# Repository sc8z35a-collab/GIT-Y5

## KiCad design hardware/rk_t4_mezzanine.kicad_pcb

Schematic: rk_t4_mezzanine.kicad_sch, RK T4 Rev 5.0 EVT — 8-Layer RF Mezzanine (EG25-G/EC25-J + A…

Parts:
C701, C702, C705, C706: GRM0335C1H101JA01D; 0201
C753, C754, C1332, C1338, C1339, C1340, C1343, C1345, C1346, C1348, C1351, C1352, C1355, C1357, C1358, C1360, C1361, C1363, C1366, C1367, C1370, C1372, C1373, C1375, C1376, C1378, C1381, C1382, C1385, C1387, C1388, C1391: GRM033R61A104KE15D; 0201
C1322, C1328, C1331, C1333, C1334, C1335, C1336, C1337: GRM033R60J105MEA2D; 0201
C1323, C1324, C1329, C1330: GRM0335C1H120JA01D; 0201
C1325, C1326: GRM155R61A475MEAA; 0402
C1327: GRM155R61A106ME44D; 0402
C1341, C1342: GRM033R60J225ME15D; 0201
C1344, C1349, C1354, C1359, C1364, C1369, C1374, C1379, C1384: GRM155R60J226ME11D; 0402
C1347, C1350, C1353, C1356, C1362, C1365, C1368, C1371, C1377, C1380, C1383, C1386: GRM022R60J103ME15; 01005
FB1011, FB1012: BLM03AG121SN1D; 0201
J701, J702, J705, J706, J707: 20449-001E; MHF4-RECEPT
J708A, J708B: 2329497-2; TE-2329497-2
J901A, J901B: DF40C-40DP-0.4V(51); DF40C-40DP
L701, L702: DFE201610E-0R56M=P2; IND_1608
L711, L712: DFE201610E-2R2M=P2; IND_1608
L1001, L1002: LQG15HS47NJ02D; 0201
Q701, Q702: BSS138; SOT-23__2.9x2.4mm_
R133: RC0201FR-0710KL; 0201
R1007, R1008: RC0201FR-07100KL; 0201
R1009, R1010: RC0201FR-071KL; 0201
R1011, R1012: RC0201FR-07470RL; 0201
RT701: NCP03XH103F05RL; 0201
TP701, TP702: TP_0.8MM_ENIG; TP_0.8MM
U701: EG25-G; LGA-144__29.0x32.0mm_
U707: AP6275P; LGA-50__15.0x13.0mm_
U708: MIA-M10Q-00B; LGA-54__4.5x4.5mm_
U710: PN7160A1HN; HVQFN-40__6.0x6.0mm_
U715: IQS7222A001QNR; QFN-20__3.0x3.0mm_
U716: STSAFE-A110; UFDFPN8__2.0x3.0mm_
Y701: NX2016SA-27.12M; SMD-2016
Y702: NX2016SA-37.4M; SMD-2016

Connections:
BT_HOST_WAKE: J901B.31, U707.50 (BT_HOST_WAKE)
BT_REG_ON: J901B.29, U707.38 (BT_REG_ON)
BT_UART_CTS_N: J901B.36, U707.42 (BT_UART_RTS_N)
BT_UART_RTS_N: J901B.35, U707.43 (BT_UART_CTS_N)
BT_UART_RX: J901B.34, U707.40 (BT_UART_TXD)
BT_UART_TX: J901B.33, U707.41 (BT_UART_RXD)
BT_WAKE: J901B.30, U707.49 (BT_WAKE)
CLK_32K_RTC: J901B.32, U707.31 (LPO_IN)
EG_PWRKEY_N: Q701.3 (D), U701.21 (PWRKEY)
EG_RESET_N: Q702.3 (D), U701.20 (RESET_N)
EG_VDD_EXT_1V8: C1322.1, U701.7 (VDD_EXT)
ESE_RST_N: J901A.40, U716.8 (RESET)
GND: C1322.2, C1323.2, C1324.2, C1325.2, C1326.2, C1327.2, C1328.2, C1329.2, C1330.2, C1331.2, C1332.2, C1333.2, C1334.2, C1335.2, C1336.2, C1337.2, C1338.2, C1339.2, C1340.2, C1341.2, C1342.2, C1343.2, C1344.2, C1345.2, C1346.2, C1347.2, C1348.2, C1349.2, C1350.2, C1351.2, C1352.2, C1353.2, C1354.2, C1355.2, C1356.2, C1357.2, C1358.2, C1359.2, C1360.2, C1361.2, C1362.2, C1363.2, C1364.2, C1365.2, C1366.2, C1367.2, C1368.2, C1369.2, C1370.2, C1371.2, C1372.2, C1373.2, C1374.2, C1375.2, C1376.2, C1377.2, C1378.2, C1379.2, C1380.2, C1381.2, C1382.2, C1383.2, C1384.2, C1385.2, C1386.2, C1387.2, C1388.2, C1391.2, J701.2 (GND_1), J701.3 (GND_2), J702.2 (GND_1), J702.3 (GND_2), J705.2 (GND_1), J705.3 (GND_2), J706.2 (GND_1), J706.3 (GND_2), J707.2 (GND_1), J707.3 (GND_2), J901A.7, J901A.8, J901A.10, J901A.12, J901A.19, J901A.20, J901A.30, J901A.34, J901B.11, J901B.12, J901B.14, J901B.16, J901B.18, J901B.20, J901B.22, J901B.24, Q701.2 (S), Q702.2 (S), R1007.2, R1008.2, RT701.2, U701.8 (GND), U701.9 (GND), U701.10 (USIM_GND), U701.19 (GND), U701.22 (GND), U701.36 (GND), U701.46 (GND), U701.48 (GND), U701.50 (GND), U701.51 (GND), U701.52 (GND), U701.53 (GND), U701.54 (GND), U701.56 (GND), U701.72 (GND), U701.85 (GND), U701.86 (GND), U701.87 (GND), U701.88 (GND), U701.89 (GND), U701.90 (GND), U701.91 (GND), U701.92 (GND), U701.93 (GND), U701.94 (GND), U701.95 (GND), U701.96 (GND), U701.97 (GND), U701.98 (GND), U701.99 (GND), U701.100 (GND), U701.101 (GND), U701.102 (GND), U701.103 (GND), U701.104 (GND), U701.105 (GND), U701.106 (GND), U701.107 (GND), U701.108 (GND), U701.109 (GND), U701.110 (GND), U701.111 (GND), U701.112 (GND), U707.1 (GND), U707.3 (GND), U707.4 (GND), U707.5 (GND), U707.6 (GND), U707.7 (GND), U707.8 (GND), U707.10 (GND), U707.11 (GND), U707.23 (GND), U707.27 (GND), U707.30 (GND), U707.32 (GND), U707.39 (GND), U708.A1 (GND), U708.A2 (GND), U708.A3 (GND), U708.A5 (RTC_O), U708.A8 (GND), U708.A9 (GND), U708.B2 (GND), U708.B8 (GND), U708.C3 (GND), U708.C9 (GND), U708.E3 (GND), U708.E4 (GND), U708.E9 (GND), U708.F1 (GND), U708.F3 (GND), U708.F4 (GND), U708.F9 (GND_0R), U708.G3 (GND), U708.G4 (GND), U708.G5 (GND), U708.G6 (GND), U708.G7 (GND_0R), U708.H8 (GND), U708.J6 (VIO_SEL), U708.J8 (GND), U708.J9 (GND), U710.1 (I2C_ADR0), U710.3 (I2C_ADR1), U710.4 (VSS_PAD), U710.9 (VSS_A), U710.20 (VSS_TX), U710.41 (EP_VSS), U715.3 (VSS), U715.21 (EP_VSS), U716.4 (GND), Y701.2 (GND_1), Y701.4 (GND_2), Y702.2 (GND_1), Y702.4 (GND_2)
GNSS_ANT_50: J707.1 (SIG), U708.B9 (RF_IN)
GNSS_RST_N: J901A.33, U708.C4 (RESET_N)
GNSS_UART_RX: J901A.32, U708.G1 (TXD)
GNSS_UART_TX: J901A.31, U708.H1 (RXD)
I2C5_SCL: J901B.37, U710.7 (I2C_SCL), U716.7 (SCL)
I2C5_SDA: J901B.38, U710.5 (I2C_SDA), U716.5 (SDA)
I2C6_SCL: J901A.35, U715.18 (SCL)
I2C6_SDA: J901A.36, U715.19 (SDA)
LTE_ANT_DIV_RAW: C702.1, U701.35 (ANT_DIV)
LTE_ANT_RF_RAW: C701.1, U701.49 (ANT_MAIN)
MIA_D2_E2: U708.D2 (D2_TIE_E2), U708.E2 (E2_TIE_D2)
MODEM_NET_STATUS: J901A.18, U701.6 (NET_STATUS)
MODEM_PWRKEY_EN: J901A.15, Q701.1 (G), R1007.1
MODEM_RESET_EN: J901A.16, Q702.1 (G), R1008.1
MODEM_STATUS: J901A.17, U701.61 (STATUS)
MODEM_UART_RX: J901A.14, U701.67 (TXD)
MODEM_UART_TX: J901A.13, U701.68 (RXD)
MODEM_USB_DN: J901A.11, U701.70 (USB_DM)
MODEM_USB_DP: J901A.9, U701.69 (USB_DP)
NFC_27M_XI: C1329.1, U710.30 (XTAL1), Y701.1 (X1)
NFC_27M_XO: C1330.1, U710.29 (XTAL2), Y701.3 (X2)
NFC_ANT_N: C1339.1, J708B.1, L702.2, R1010.1
NFC_ANT_P: C1338.1, J708A.1, L701.2, R1009.1
NFC_DWL_REQ: J901A.39, U710.2 (DWL_REQ)
NFC_IRQ: J901B.39, U710.8 (IRQ)
NFC_RXN: R1010.2, U710.15 (RXN)
NFC_RXP: R1009.2, U710.16 (RXP)
NFC_TX1: L701.1, U710.21 (TX1)
NFC_TX2: L702.1, U710.19 (TX2)
NFC_VDD: C1336.1, U710.27 (VDD)
NFC_VDD_A: C1335.1, U710.26 (VDD_A)
NFC_VDD_D: C1337.1, U710.31 (VDD_D)
NFC_VDD_HF: C1334.1, U710.25 (VDD_HF)
NFC_VDD_TX: C1332.1, U710.14 (VDD_TX), U710.18 (TVDD_IN), U710.22 (TVDD_IN2)
NFC_VDD_UP: C1331.1, U710.13 (VDD_UP)
NFC_VEN: J901B.40, U710.10 (VEN)
NFC_VMID: C1333.1, U710.17 (VDD_VMID)
PCIE_WIFI_CLK_N: J901B.23, U707.33 (PCIE_RCLK_N)
PCIE_WIFI_CLK_P: J901B.21, U707.35 (PCIE_RCLK_P)
PCIE_WIFI_RX_N: J901B.19, U707.44 (PCIE_RX_N)
PCIE_WIFI_RX_P: J901B.17, U707.45 (PCIE_RX_P)
PCIE_WIFI_TX_AC_N: C754.2, U707.46 (PCIE_TX_N)
PCIE_WIFI_TX_AC_P: C753.2, U707.47 (PCIE_TX_P)
PCIE_WIFI_TX_N: C754.1, J901B.15
PCIE_WIFI_TX_P: C753.1, J901B.13
PCM_MODEM_CLK: J901A.21, U701.27 (PCM_CLK)
PCM_MODEM_RX: J901A.24, U701.25 (PCM_OUT)
PCM_MODEM_SYNC: J901A.22, U701.26 (PCM_SYNC)
PCM_MODEM_TX: J901A.23, U701.24 (PCM_IN)
RF_ANT_DIV_50: C702.2, J702.1 (SIG)
RF_ANT_MAIN_50: C701.2, J701.1 (SIG)
SAR_CRX0_L: L1001.1, R1011.2
SAR_CRX0_R: R1011.1, U715.5 (CRX0)
SAR_CRX1_L: L1002.1, R1012.2
SAR_CRX1_R: R1012.1, U715.6 (CRX1)
SAR_INT_N: J901A.37, U715.17 (RDY)
SAR_MCLR: C1343.1, U715.20 (MCLR)
SAR_PAD_0: L1001.2, TP701.1
SAR_PAD_1: L1002.2, TP702.1
SAR_VREGA: C1342.1, U715.4 (VREGA)
SAR_VREGD: C1341.1, U715.2 (VREGD)
THERM_RFPA_ADC: C1391.1, J901A.38, R133.1, RT701.1
USIM1_CLK: J901A.26, U701.16 (USIM_CLK)
USIM1_DET: J901A.29, U701.13 (USIM_PRESENCE)
USIM1_IO: J901A.28, U701.15 (USIM_DATA)
USIM1_RST: J901A.27, U701.17 (USIM_RST)
USIM1_VCC: J901A.25, U701.14 (USIM_VDD)
VCC_1V8_GNSS: C1328.1, C1348.1, C1353.1, C1358.1, C1363.1, C1368.1, C1373.1, C1378.1, C1383.1, C1388.1, FB1012.2, U708.B1 (VCC), U708.J4 (V_IO), U708.J5 (V_BCKP)
VCC_1V8_S3: C1340.1, C1346.1, C1351.1, C1356.1, C1361.1, C1366.1, C1371.1, C1376.1, C1381.1, C1386.1, FB1012.1, J901B.7, J901B.8, J901B.9, J901B.10, R133.2, U707.34 (VDDIO), U710.6 (VDD_PAD), U715.1 (VDD), U716.2 (VCC)
VCC_3V3_S3: C1345.1, C1350.1, C1355.1, C1360.1, C1365.1, C1370.1, C1375.1, C1380.1, C1385.1, FB1011.1, J901B.1, J901B.2, J901B.3, J901B.4, J901B.5, J901B.6, U701.71 (USB_VBUS)
VCC_3V3_WIFI: C1327.1, C1347.1, C1352.1, C1357.1, C1362.1, C1367.1, C1372.1, C1377.1, C1382.1, C1387.1, FB1011.2, U707.36 (VBAT)
VSYS_3V87: C1344.1, C1349.1, C1354.1, C1359.1, C1364.1, C1369.1, C1374.1, C1379.1, C1384.1, J901A.1, J901A.2, J901A.3, J901A.4, J901A.5, J901A.6, U701.57 (VBAT_RF_1), U701.58 (VBAT_RF_2), U701.59 (VBAT_BB_1), U701.60 (VBAT_BB_2), U710.12 (VBAT2), U710.28 (VBAT)
WIFI_37M_XI: C1323.1, U707.14 (XTAL_XON), Y702.1 (X1)
WIFI_37M_XO: C1324.1, U707.13 (XTAL_XOP), Y702.3 (X2)
WIFI_ABUCK_1P12: C1326.1, L712.2, U707.29 (ABUCK_1P12)
WIFI_ANT0_50: C705.2, J705.1 (SIG)
WIFI_ANT0_RAW: C705.1, U707.2 (WL_ANT0)
WIFI_ANT1_50: C706.2, J706.1 (SIG)
WIFI_ANT1_RAW: C706.1, U707.9 (WL_ANT1)
WIFI_ASR_VLX: L712.1, U707.28 (ASR_VLX)
WIFI_CBUCK_0P9: C1325.1, L711.2, U707.25 (CBUCK_0P9)
WIFI_CLKREQ_N: J901B.27, U707.37 (PCIE_CLKREQ_L)
WIFI_CSR_VLX: L711.1, U707.26 (CSR_VLX)
WIFI_PERST_N: J901B.25, U707.12 (PCIE_PERST_L)
WIFI_REG_ON: J901B.28, U707.15 (WL_REG_ON)
WIFI_WAKE_N: J901B.26, U707.16 (WL_HOST_WAKE), U707.24 (PCIE_PME_L)

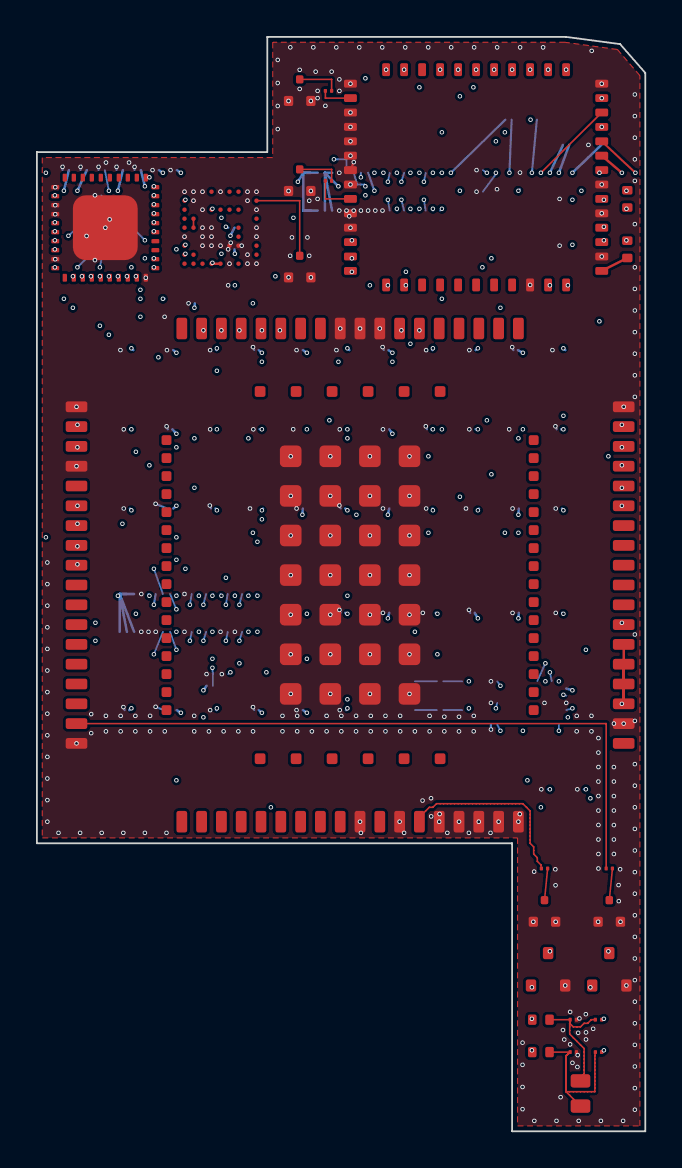
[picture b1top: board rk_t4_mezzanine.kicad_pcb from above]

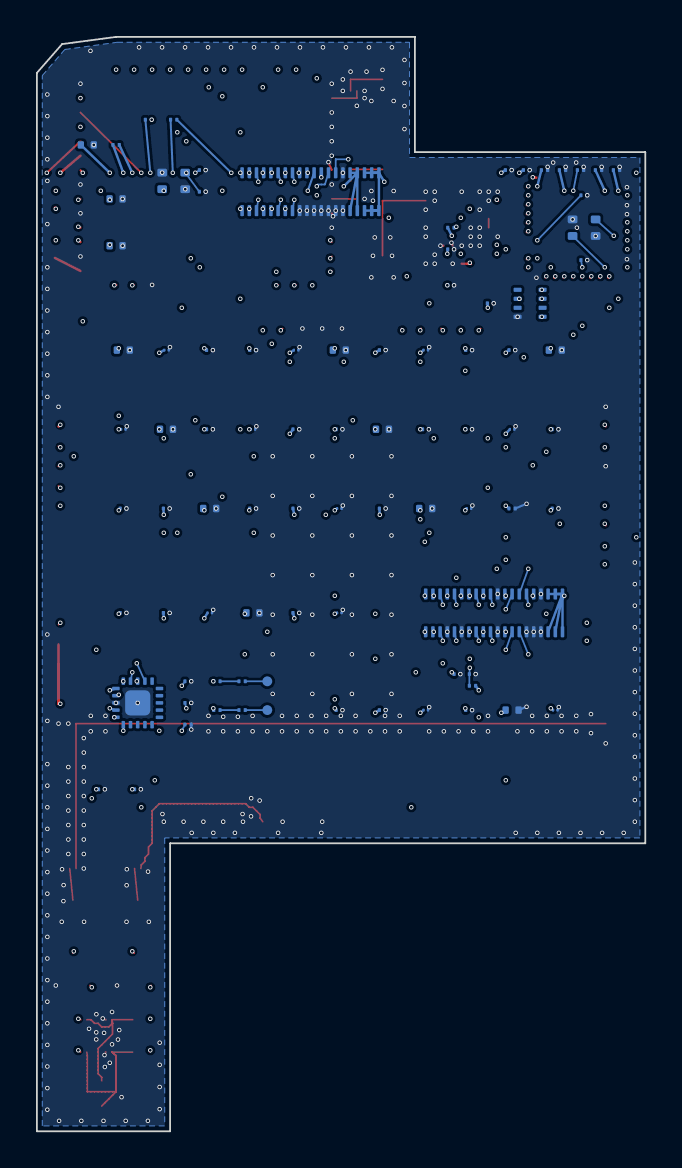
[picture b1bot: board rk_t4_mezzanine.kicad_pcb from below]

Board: 8 copper layers, 33.8 x 60.8 mm, 111 parts (86 on the bottom side), 99 nets.

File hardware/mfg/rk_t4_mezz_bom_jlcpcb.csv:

Comment,Designator,Footprint,LCSC Part #
DF40C-40DP-0.4V(51),"J901A,J901B",DF40C-40DP,
EG25-G,U701,LGA-144 (29.0x32.0mm),
BSS138,"Q701,Q702",SOT-23 (2.9x2.4mm),
RC0201FR-07100KL,"R1007,R1008",0201,C106224
GRM033R60J105MEA2D,"C1322,C1328,C1331,C1333,C1334,C1335,C1336,C1337",0201,C76930
GRM0335C1H101JA01D,"C701,C702,C705,C706",0201,C76922
20449-001E,"J701,J702,J705,J706,J707",MHF4-RECEPT,
AP6275P,U707,LGA-50 (15.0x13.0mm),
NX2016SA-37.4M,Y702,SMD-2016,
GRM0335C1H120JA01D,"C1323,C1324,C1329,C1330",0201,C85890
DFE201610E-2R2M=P2,"L711,L712",IND_1608,C337891
GRM155R61A475MEAA,"C1325,C1326",0402,C335105
BLM03AG121SN1D,"FB1011,FB1012",0201,C97850
GRM155R61A106ME44D,C1327,0402,C77000
GRM033R61A104KE15D,"C753,C754,C1332,C1338,C1339,C1340,C1343,C1345,C1346,C1348,C1351,C1352,C1355,C1357,C1358,C1360,C1361,C1363,C1366,C1367,C1370,C1372,C1373,C1375,C1376,C1378,C1381,C1382,C1385,C1387,C1388,C1391",0201,C76934
MIA-M10Q-00B,U708,LGA-54 (4.5x4.5mm),
PN7160A1HN,U710,HVQFN-40 (6.0x6.0mm),
NX2016SA-27.12M,Y701,SMD-2016,
DFE201610E-0R56M=P2,"L701,L702",IND_1608,
RC0201FR-071KL,"R1009,R1010",0201,C138165
2329497-2,"J708A,J708B",TE-2329497-2,C693052
STSAFE-A110,U716,UFDFPN8 (2.0x3.0mm),
IQS7222A001QNR,U715,QFN-20 (3.0x3.0mm),
GRM033R60J225ME15D,"C1341,C1342",0201,C398930
RC0201FR-07470RL,"R1011,R1012",0201,
LQG15HS47NJ02D,"L1001,L1002",0201,
TP_0.8MM_ENIG,"TP701,TP702",TP_0.8MM,
GRM155R60J226ME11D,"C1344,C1349,C1354,C1359,C1364,C1369,C1374,C1379,C1384",0402,C415703
GRM022R60J103ME15,"C1347,C1350,C1353,C1356,C1362,C1365,C1368,C1371,C1377,C1380,C1383,C1386",01005,
NCP03XH103F05RL,RT701,0201,C98098
RC0201FR-0710KL,R133,0201,C106225
